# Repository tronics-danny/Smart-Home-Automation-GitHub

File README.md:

# Smart Home Automation

Welcome to the Smart Home Automation project. This system provides automated control and monitoring for various aspects of your home.

## Features

**Automatic Door Control **:
- This feature allows you to restrict who can have access to your home. You will be required to know the password or have an RFID card to access the main door.

**Controlled Lighting**:
- Our system enables you to control and monitor in real-time the lighting in your home. On detecting the presence of a person in a certain room, the lights will go on automatically unless manually overridden or switched off via the monitoring app.

**Smoke Detection Alarm**:
- The smoke detection alarm feature helps protect your home by monitoring for smoke and alerting you in case of an emergency.

**Room Temperature Control**:
- The system regulates room temperature using temperature sensors and can activate fans or heating devices to keep your home comfortable. You can set temperature thresholds and schedules.

**Humidity Monitoring**: 
- Humidity levels in your home are monitored, and you can configure actions to maintain ideal conditions. This may involve dehumidification or activating humidifiers.

**Remote Monitoring**:
- You can monitor and control your home from anywhere using our dedicated mobile app. Check the status of your devices and receive alerts in real-time.

**Real-time Monitoring**:
- Real-time data on the status of your home's environment is provided. You can view charts and statistics about temperature, humidity, and more.

## Usage

1. **Automatic Door Control**: Access your door by use of an RFID card or using your set password which you can share with the people you want to be able to have access to your home.

2. **Controlled Lighting**: Control your lights in the "Lighting" section. Create schedules, change brightness, or set scenes to match your mood.

3. **Smoke, Gas, and Fire Detection Alarm**: In the "Security" section, configure the smoke alarm settings and receive notifications in case of smoke, fire, or gas leak. 

4. **Room Temperature Control**: Set your desired temperature in the "Climate" section, and let the system manage the environment.

5. **Humidity Monitoring**: In the "Climate" section, monitor humidity levels and configure actions to maintain ideal conditions.

6. **Remote Monitoring**: Use the mobile app or web dashboard to monitor and control your home from anywhere.

7. **Real-time Monitoring**: Access real-time data on your home's environment in the "Monitoring" section.

## Contact

If you have questions or need support, please feel free to reach out:

- Email: dmaithya29@gmail.com
- LinkedIn: Daniel Maithya
- Instagram: @tronics_danny

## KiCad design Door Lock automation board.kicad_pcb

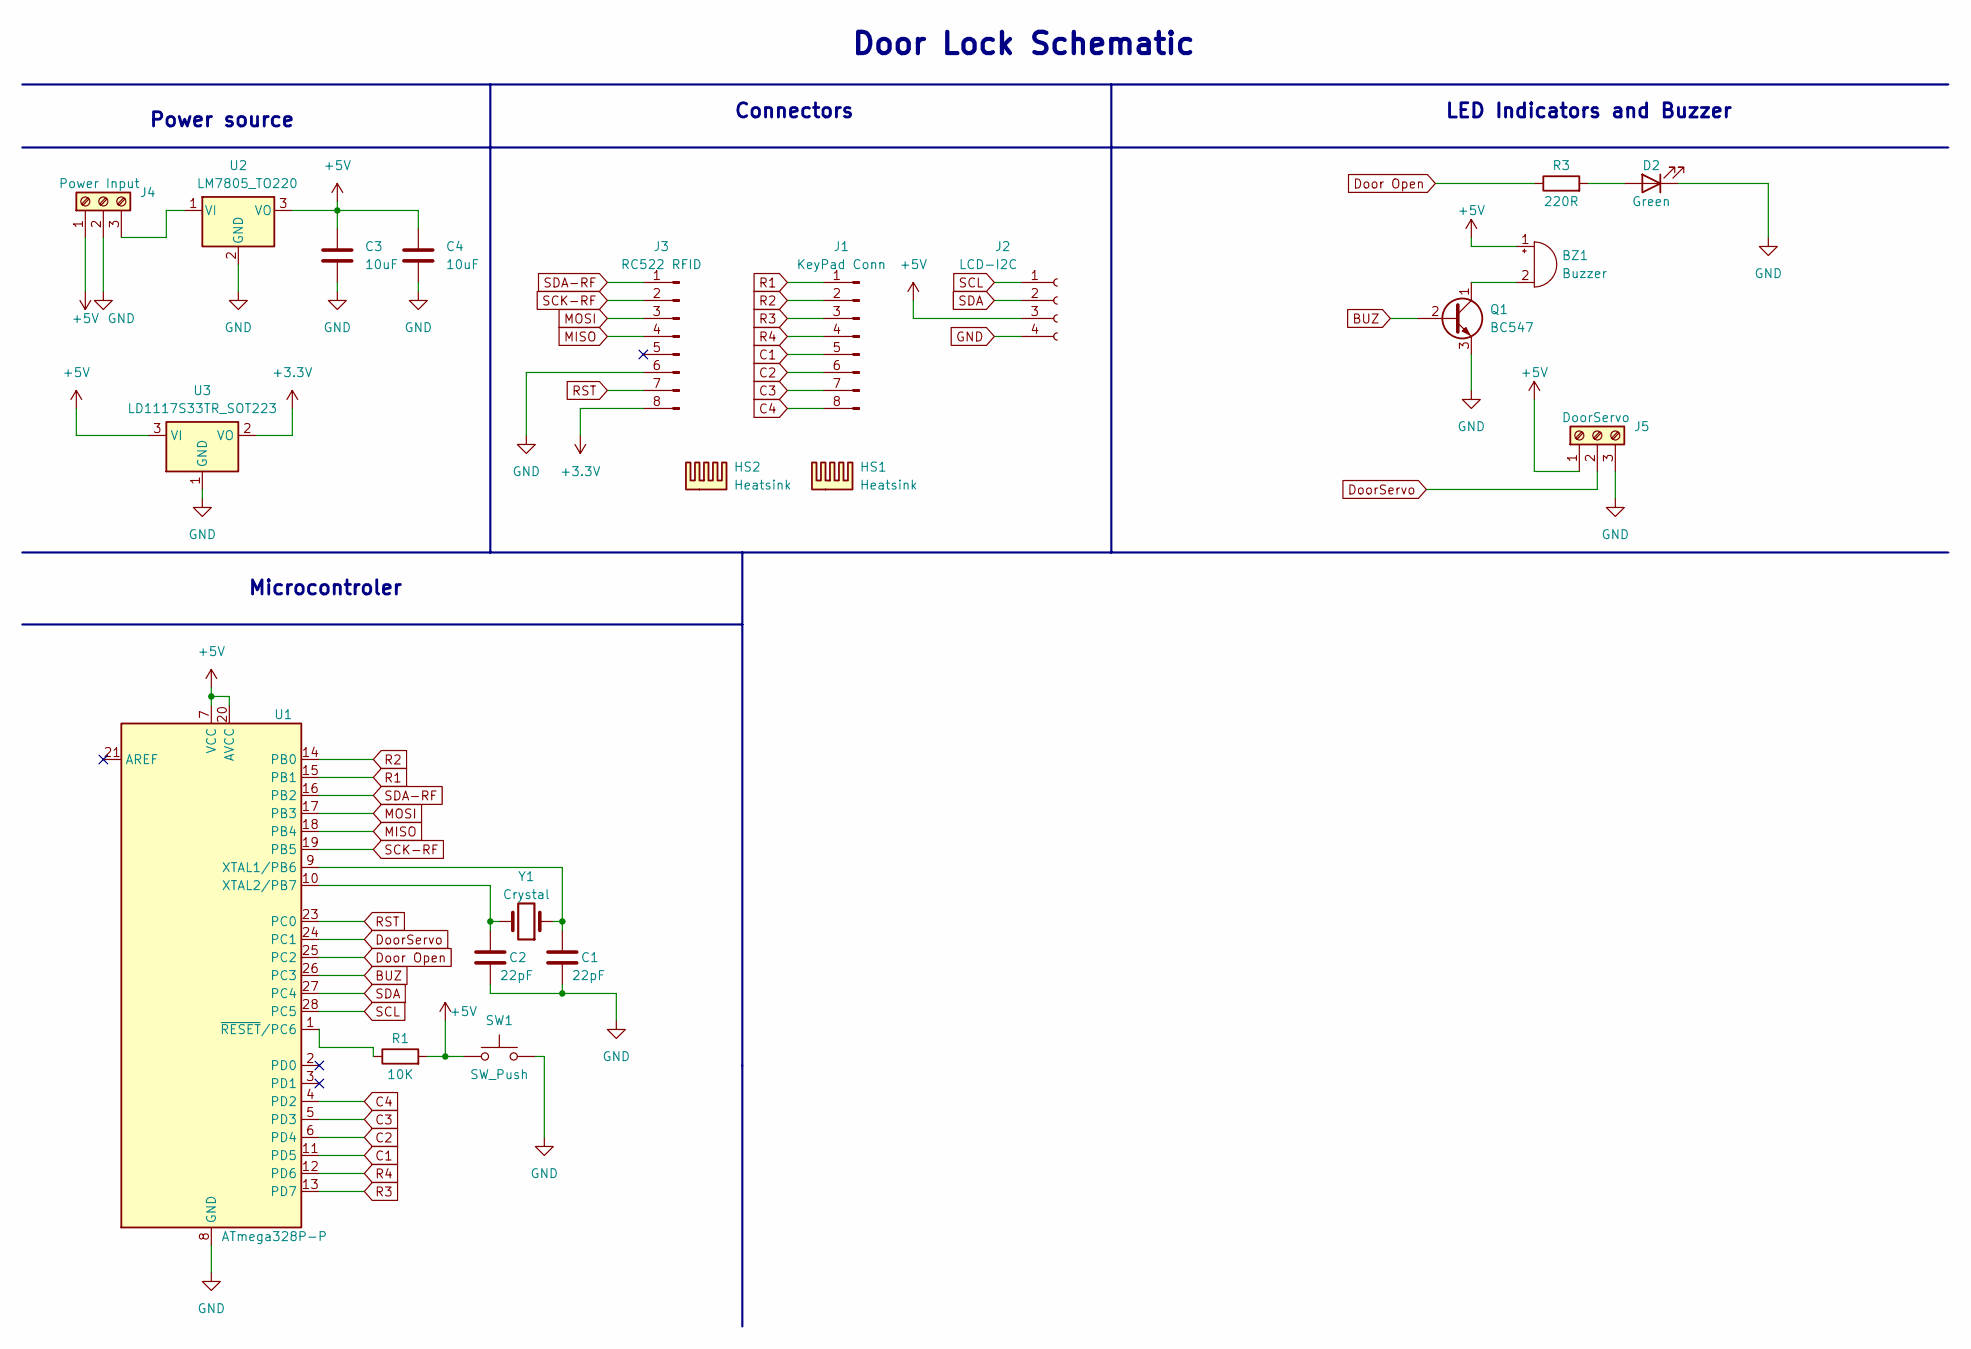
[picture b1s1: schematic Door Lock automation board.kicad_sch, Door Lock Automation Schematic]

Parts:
BZ1: Buzzer; Buzzer_12x9.5RM7.6
C1, C2: 22pF; C_Disc_D7.5mm_W2.5mm_P5.00mm
C3, C4: 10uF; C_Radial_D6.3mm_H7.0mm_P2.50mm
D2: Green; LED_D3.0mm
HS1, HS2: Heatsink; Heatsink_Stonecold_HS-S02_13.21x9.53mm
J1: KeyPad Conn; PinHeader_1x08_P1.27mm_Horizontal
J2: LCD-I2C; PinHeader_1x04_P2.54mm_Vertical
J3: RC522 RFID; PinHeader_1x08_P2.54mm_Vertical
J4: Power Input; TerminalBlock_Phoenix_PT-1,5-3-3.5-H_1x03_P3.50mm_Horizontal
J5: DoorServo; TerminalBlock_Phoenix_PT-1,5-3-3.5-H_1x03_P3.50mm_Horizontal
Q1: BC547; TO-92_Inline
R1: 10K; R_Axial_DIN0207_L6.3mm_D2.5mm_P10.16mm_Horizontal
R3: 220R; R_Axial_DIN0207_L6.3mm_D2.5mm_P10.16mm_Horizontal
SW1: SW_Push; SW_PUSH_6mm_H5mm
U1: ATmega328P-P; DIP-28_W7.62mm_Socket_LongPads
U2: LM7805_TO220; TO-220-3_Vertical
U3: LD1117S33TR_SOT223; TO-220F-3_Vertical
Y1: Crystal; Crystal_HC49-4H_Vertical

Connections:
+3.3V: J3.8, U3.2 (VO)
+5V: BZ1.1 (-), C3.1, C4.1, J2.3, J4.1, J5.1, R1.2, SW1.1, U1.7 (VCC), U1.20 (AVCC), U2.3 (VO), U3.3 (VI)
BUZ: Q1.2 (B), U1.26 (PC3)
C1: J1.5, U1.11 (PD5)
C2: J1.6, U1.6 (PD4)
C3: J1.7, U1.5 (PD3)
C4: J1.8, U1.4 (PD2)
Door Closed: J5.2, U1.24 (PC1); also elsewhere on the board
Door Open: R3.1, U1.25 (PC2)
GND: C1.2, C2.1, C3.2, C4.2, D2.1 (K), J2.4, J3.6, J4.2, J5.3, Q1.3 (E), SW1.2, U1.8 (GND), U1.22 (GND), U2.2 (GND), U3.1 (GND); also elsewhere on the board
MISO: J3.4, U1.18 (PB4)
MOSI: J3.3, U1.17 (PB3)
unnamed: BZ1.2 (+), Q1.1 (C)
unnamed: D2.2 (A), R3.2
unnamed: J4.3, U2.1 (VI)
unnamed: C1.1, U1.9 (XTAL1/PB6), Y1.1
unnamed: C2.2, U1.10 (XTAL2/PB7), Y1.2
unnamed: R1.1, U1.1 (~RESET/PC6)
R1: J1.1, U1.15 (PB1)
R2: J1.2, U1.14 (PB0)
R3: J1.3, U1.13 (PD7)
R4: J1.4, U1.12 (PD6)
RST: J3.7, U1.23 (PC0)
SCK-RF: J3.2, U1.19 (PB5)
SCL: J2.1, U1.28 (PC5)
SDA: J2.2, U1.27 (PC4)
SDA-RF: J3.1, U1.16 (PB2)

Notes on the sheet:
Connectors
Door Lock Schematic
Power source
LED Indicators and Buzzer
Microcontroler

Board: 2 copper layers, 22 parts (0 on the bottom side), 28 nets, no tracks yet.

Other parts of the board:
D1: Red; LED_D3.0mm
R2: 220R; R_Axial_DIN0207_L6.3mm_D2.5mm_P10.16mm_Horizontal

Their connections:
Door Closed: R2.1; also elsewhere on the board
GND: D1.1 (K); also elsewhere on the board
unnamed: D1.2 (A), R2.2

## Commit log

2023-11-18 Add files via upload
    Lighting Control with PIR sensors and relays
2023-11-18 Rename pirrrrrr.ino to lighting_control
